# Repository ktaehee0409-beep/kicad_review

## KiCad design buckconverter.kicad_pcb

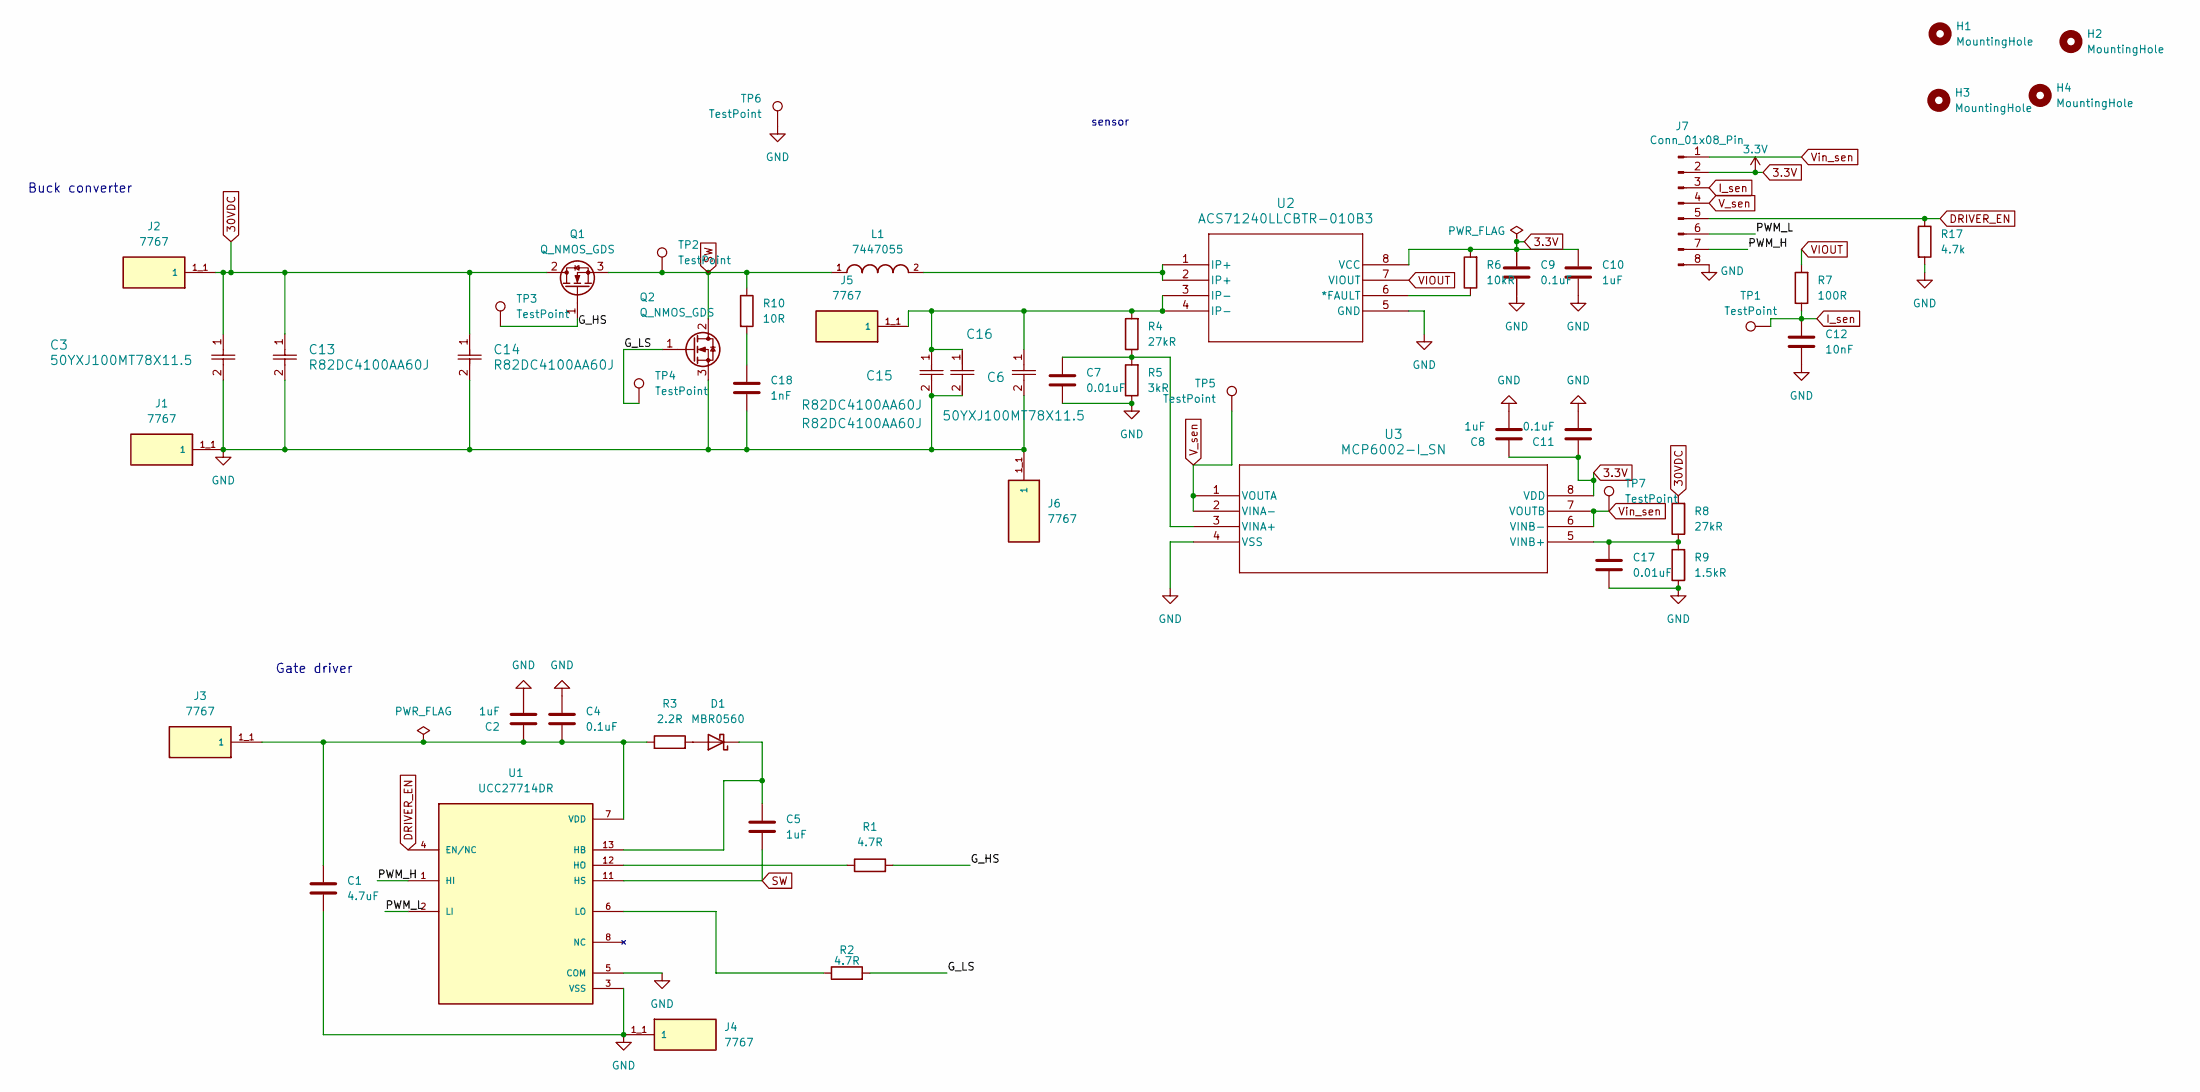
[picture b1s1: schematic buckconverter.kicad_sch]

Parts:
C1: 4.7uF; C_0805_2012Metric
C2, C5, C8, C10: 1uF; C_0805_2012Metric
C3, C6: 50YXJ100MT78X11.5; 50YXJ100MT78X11_5
C4, C9, C11: 0.1uF; C_0805_2012Metric
C7, C17: 0.01uF; C_0805_2012Metric
C12: 10nF; C_0805_2012Metric
C13, C14, C15, C16: R82DC4100AA60J
C18: 1nF; C_1206_3216Metric
D1: MBR0560; D_SOD-123
H1, H2, H3, H4: MountingHole; MountingHole_3.2mm_M3
J1, J2, J3, J4, J5, J6: 7767; KEYSTONE_7767; PARTREV B; DigiKey_Part_Number 36-7767-ND
J7: Conn_01x08_Pin; PinSocket_1x08_P2.54mm_Vertical
L1: 7447055; WE-FI_7447055
Q1, Q2: Q_NMOS_GDS; TO-220-3_Vertical
R1, R2: 4.7R; R_0805_2012Metric
R3: 2.2R; R_0805_2012Metric
R4, R8: 27kR; R_0805_2012Metric
R5: 3kR; R_0805_2012Metric
R6: 10kR; R_0805_2012Metric
R7: 100R; R_0805_2012Metric
R9: 1.5kR; R_0805_2012Metric
R10: 10R; R_1206_3216Metric
R17: 4.7k; R_0805_2012Metric
TP1, TP2, TP3, TP4, TP5, TP6, TP7: TestPoint; TestPoint_Keystone_5000-5004_Miniature
U1: UCC27714DR; PARTREV B; DigiKey_Part_Number 296-42701-1-ND
U2: ACS71240LLCBTR-010B3
U3: MCP6002-I_SN

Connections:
3.3V: C8.1, C9.1, C10.1, C11.1, J7.2, R6.2, U2.8 (VCC), U3.8 (VDD)
30VDC: C3.1, C13.1, C14.1, J2.1_1 (1), J2.1_2 (1), J2.1_3 (1), J2.1_4 (1), Q1.2 (D), R8.2
/G_HS: Q1.1 (G), R1.2, TP3.1 (1_1)
/G_LS: Q2.1 (G), R2.2, TP4.1 (1_1)
/PWM_H: J7.7, U1.1 (HI)
/PWM_L: J7.6, U1.2 (LI)
DRIVER_EN: J7.5, R17.1, U1.4 (EN/NC)
GND: C1.2, C2.2, C3.2, C4.1, C6.2, C7.2, C8.2, C9.2, C10.2, C11.2, C12.2, C13.2, C14.2, C15.2, C16.2, C17.2, C18.2, J1.1_1 (1), J1.1_2 (1), J1.1_3 (1), J1.1_4 (1), J4.1_1 (1), J4.1_2 (1), J4.1_3 (1), J4.1_4 (1), J6.1_1 (1), J6.1_2 (1), J6.1_3 (1), J6.1_4 (1), J7.8, Q2.3 (S), R5.1, R9.1, R17.2, TP6.1 (1_1), U1.3 (VSS), U1.5 (COM), U2.5 (GND), U3.4 (VSS)
I_sen: C12.1, J7.3, R7.1, TP1.1 (1_1)
unnamed: C6.1, C15.1, C16.1, J5.1_1 (1), J5.1_2 (1), J5.1_3 (1), J5.1_4 (1), R4.2, U2.3 (IP-), U2.4 (IP-)
unnamed: C18.1, R10.2
unnamed: D1.2 (A), R3.2
unnamed: C5.1, D1.1 (K), U1.13 (HB)
unnamed: L1.2, U2.1 (IP+), U2.2 (IP+)
unnamed: R1.1, U1.12 (HO)
unnamed: R2.1, U1.6 (LO)
unnamed: C1.1, C2.1, C4.2, J3.1_1 (1), J3.1_2 (1), J3.1_3 (1), J3.1_4 (1), R3.1, U1.7 (VDD)
unnamed: R6.1, U2.6 (*FAULT)
unnamed: C7.1, R4.1, R5.2, U3.3 (VINA+)
unnamed: C17.1, R8.1, R9.2, U3.5 (VINB+)
SW: C5.2, L1.1, Q1.3 (S), Q2.2 (D), R10.1, TP2.1 (1_1), U1.11 (HS)
VIOUT: R7.2, U2.7 (VIOUT)
V_sen: J7.4, TP5.1 (1_1), U3.1 (VOUTA), U3.2 (VINA-)
Vin_sen: J7.1, TP7.1 (1_1), U3.6 (VINB-), U3.7 (VOUTB)

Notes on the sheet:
Buck converter
sensor
Gate driver

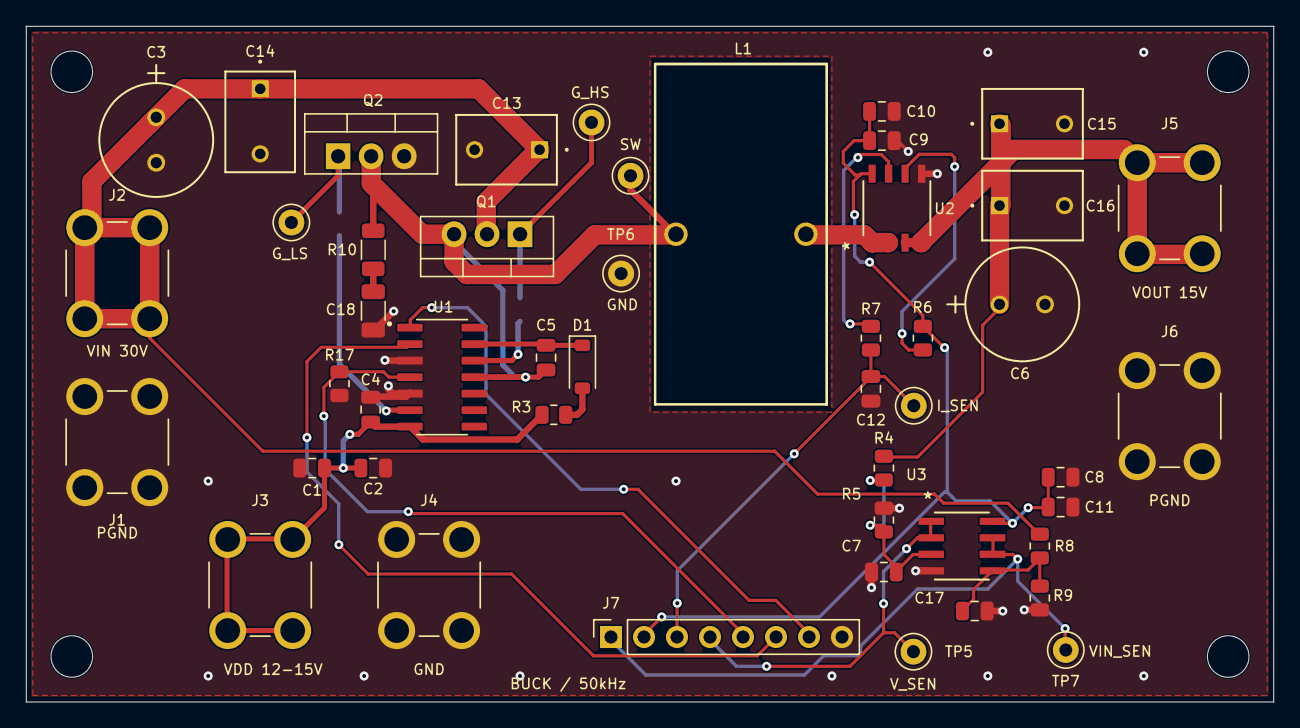
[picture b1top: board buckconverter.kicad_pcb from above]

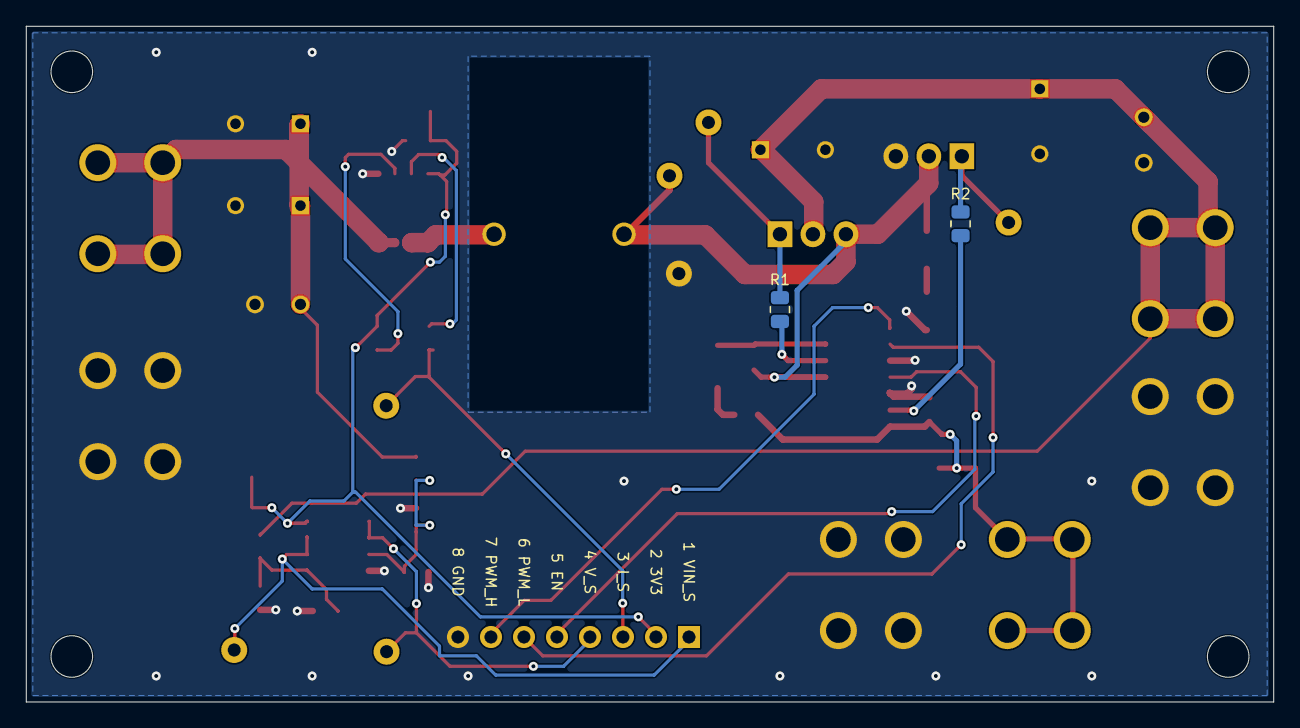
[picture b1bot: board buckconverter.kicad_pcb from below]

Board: 2 copper layers, 96.0 x 52.0 mm, 54 parts (2 on the bottom side), 24 nets.
